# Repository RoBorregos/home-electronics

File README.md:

# home-electronics:omnibase
Electronics @HOME area, new omnibase ros2 development workspace 

For documentation check the README.md in Docs_omnibase

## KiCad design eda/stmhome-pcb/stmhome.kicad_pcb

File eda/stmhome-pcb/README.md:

# stmhome

Placa de control basada en STM32H755ZIT6, diseñada en KiCad 10.

## Contenido principal

- **STM32H755ZITx** (U1), microcontrolador principal
- **ESP32-S3-WROOM-1U** (U6), Wi-Fi / Bluetooth
- **BNO086** (U4), IMU de 9 ejes
- **TJA1051T-3** (U5), transceptor CAN
- Regulador AP7361C-33E (3.3 V), protección de polaridad con P-MOSFET y TVS en +5 V

PCB de 4 capas (100 x 85 mm): F.Cu y B.Cu para señales, In1 = GND, In2 = +3.3 V.

## Estructura

| Archivo / carpeta | Descripción |
|---|---|
| `stmhome.kicad_pro` | Proyecto de KiCad (ábrelo primero) |
| `stmhome.kicad_sch` | Hoja principal (alimentación y conectores) |
| `stm.kicad_sch` | STM32H755 |
| `esp.kicad_sch` | ESP32-S3 |
| `can.kicad_sch` | Bus CAN |
| `bno085.kicad_sch` | IMU BNO086 |
| `stmhome.kicad_pcb` | Layout de la PCB |
| `libsCH340C/` | Símbolos, footprints y modelos 3D propios |
| `scripts/` | Scripts de Python usados para acomodar componentes |

## Abrir el proyecto

1. Instala KiCad 10.
2. Abre `stmhome.kicad_pro`.
3. Si algún símbolo o footprint aparece faltante, agrega las librerías de `libsCH340C/` en
   *Preferencias > Administrar librerías de símbolos / footprints* usando la ruta
   `${KIPRJMOD}/libsCH340C/...`.

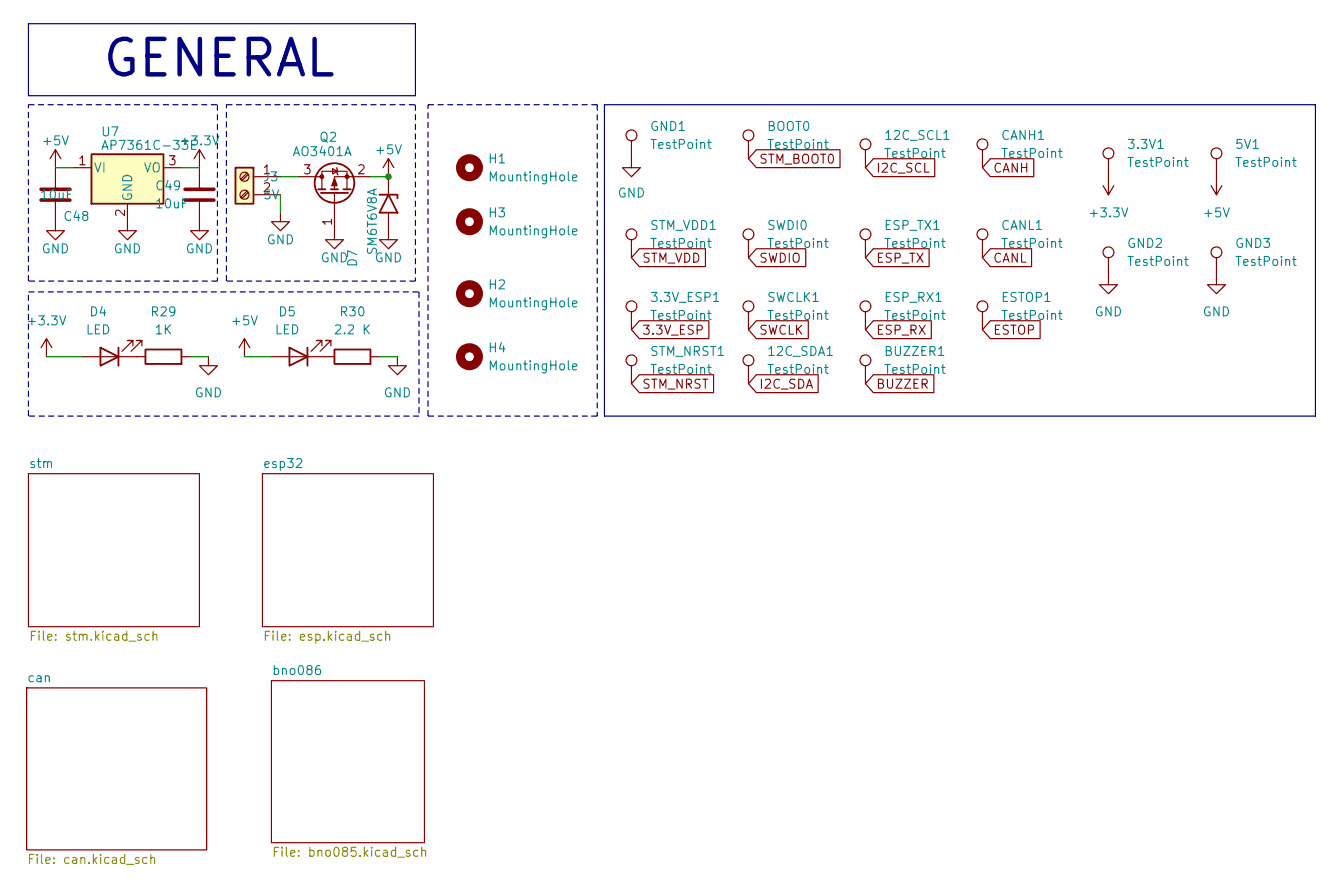
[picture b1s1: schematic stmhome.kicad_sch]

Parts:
3.3V1, 3.3V_ESP1, 5V1, 12C_SCL1, 12C_SDA1: TestPoint; TestPoint_Pad_D1.5mm
BOOT0: TestPoint; TestPoint_Pad_D1.5mm
BUZZER1: TestPoint; TestPoint_Pad_D1.5mm
C48, C49: 10uF; C_0805_2012Metric
CANH1: TestPoint; TestPoint_Pad_D1.5mm
CANL1: TestPoint; TestPoint_Pad_D1.5mm
D4, D5: LED; LED_0805_2012Metric
D7: SM6T6V8A; D_SMB
ESP_RX1: TestPoint; TestPoint_Pad_D1.5mm
ESP_TX1: TestPoint; TestPoint_Pad_D1.5mm
ESTOP1: TestPoint; TestPoint_Pad_D1.5mm
GND1, GND2, GND3: TestPoint; TestPoint_Pad_D1.5mm
H1, H2, H3, H4: MountingHole; MountingHole_3.2mm_M3
J3: 5V; TerminalBlock_Phoenix_MKDS-1,5-2-5.08_1x02_P5.08mm_Horizont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
Q2: AO3401A; SOT-23
R29: 1K; R_0805_2012Metric
R30: 2.2 K; R_0805_2012Metric
STM_NRST1: TestPoint; TestPoint_Pad_D1.5mm
STM_VDD1: TestPoint; TestPoint_Pad_D1.5mm
SWCLK1: TestPoint; TestPoint_Pad_D1.5mm
SWDI0: TestPoint; TestPoint_Pad_D1.5mm
U7: AP7361C-33E; SOT-223-3_TabPin2

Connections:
3.3V_ESP: 3.3V1.1 (1_1), 3.3V_ESP1.1 (1_1), C49.1, D4.2 (A), STM_VDD1.1 (1_1), U7.3 (VO); also elsewhere on the board
+5V: 5V1.1 (1_1), C48.1, D5.2 (A), D7.1 (A1), Q2.2 (S), U7.1 (VI); also elsewhere on the board
BUZZER: BUZZER1.1 (1_1); also elsewhere on the board
CANH: CANH1.1 (1_1); also elsewhere on the board
CANL: CANL1.1 (1_1); also elsewhere on the board
ESP_RX: ESP_RX1.1 (1_1); also elsewhere on the board
ESP_TX: ESP_TX1.1 (1_1); also elsewhere on the board
ESTOP: ESTOP1.1 (1_1); also elsewhere on the board
GND: C48.2, C49.2, D7.2 (A2), GND1.1 (1_1), GND2.1 (1_1), GND3.1 (1_1), J3.2, Q2.1 (G), R29.2, R30.2, U7.2 (GND); also elsewhere on the board
I2C_SCL: 12C_SCL1.1 (1_1); also elsewhere on the board
I2C_SDA: 12C_SDA1.1 (1_1); also elsewhere on the board
unnamed: D4.1 (K), R29.1
unnamed: D5.1 (K), R30.1
unnamed: J3.1, Q2.3 (D)
STM_BOOT0: BOOT0.1 (1_1); also elsewhere on the board
STM_NRST: STM_NRST1.1 (1_1); also elsewhere on the board
SWCLK: SWCLK1.1 (1_1); also elsewhere on the board
SWDIO: SWDI0.1 (1_1); also elsewhere on the board

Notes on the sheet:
GENERAL

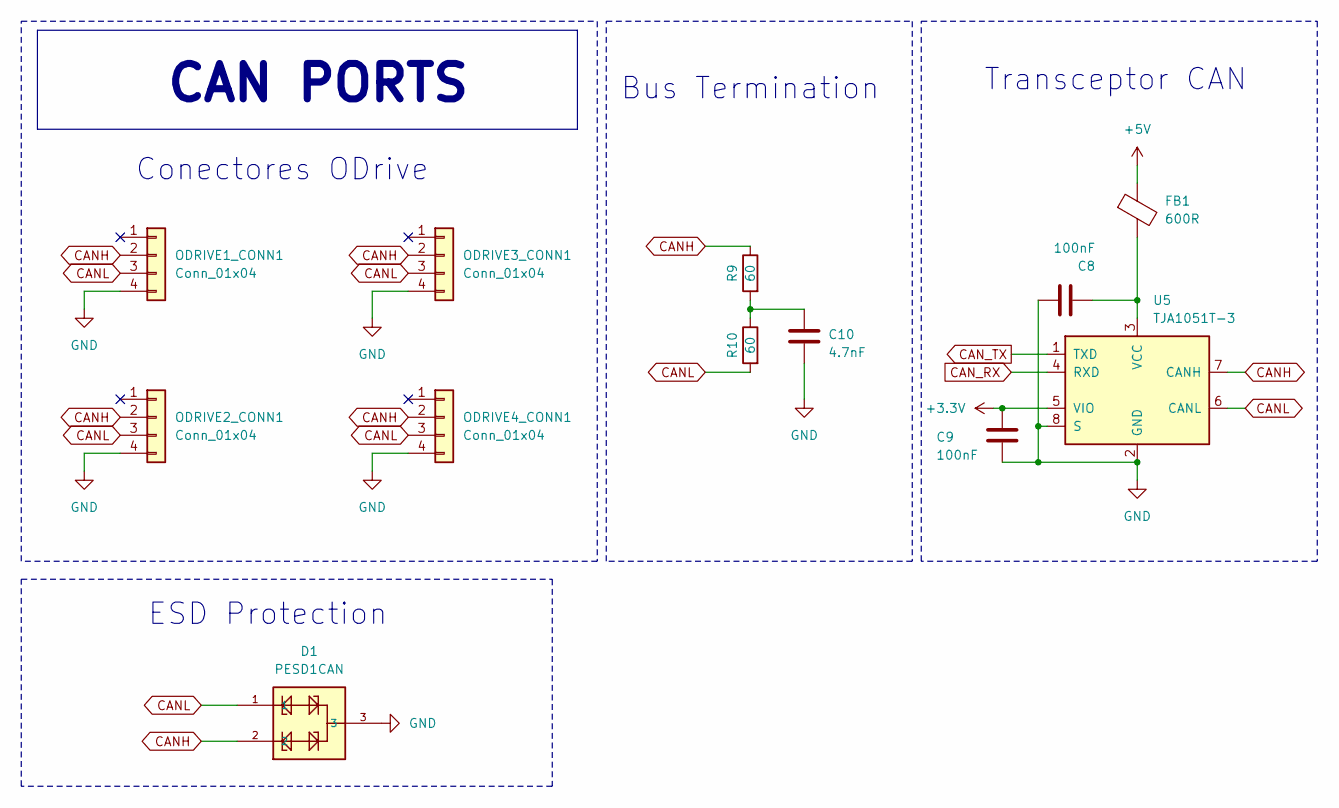
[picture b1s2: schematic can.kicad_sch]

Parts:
C8, C9: 100nF; C_0805_2012Metric
C10: 4.7nF; C_0805_2012Metric
D1: PESD1CAN; SOT23-3
FB1: 600R; L_0805_2012Metric
ODRIVE1_CONN1, ODRIVE2_CONN1, ODRIVE3_CONN1, ODRIVE4_CONN1: Conn_01x04; JST_GH_SM04B-GHS-TB_1x04-1MP_P1.25mm_Horizontal
R9, R10: 60; R_0805_2012Metric
U5: TJA1051T-3; SOIC-8_3.9x4.9mm_P1.27mm

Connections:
3.3V_ESP: C9.1, U5.5 (VIO); also elsewhere on the board
+5V: FB1.1; also elsewhere on the board
CANH: D1.2, ODRIVE1_CONN1.2, ODRIVE2_CONN1.2, ODRIVE3_CONN1.2, ODRIVE4_CONN1.2, R9.1, U5.7 (CANH); also elsewhere on the board
CANL: D1.1, ODRIVE1_CONN1.3, ODRIVE2_CONN1.3, ODRIVE3_CONN1.3, ODRIVE4_CONN1.3, R10.2, U5.6 (CANL); also elsewhere on the board
CAN_RX: U5.4 (RXD); also elsewhere on the board
CAN_TX: U5.1 (TXD); also elsewhere on the board
GND: C8.1, C9.2, C10.2, D1.3, ODRIVE1_CONN1.4, ODRIVE2_CONN1.4, ODRIVE3_CONN1.4, ODRIVE4_CONN1.4, U5.2 (GND), U5.8 (S); also elsewhere on the board
unnamed: C10.1, R9.2, R10.1
unnamed: C8.2, FB1.2, U5.3 (VCC)

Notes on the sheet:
CAN PORTS
ESD Protection
Bus Termination
Conectores ODrive
Transceptor CAN

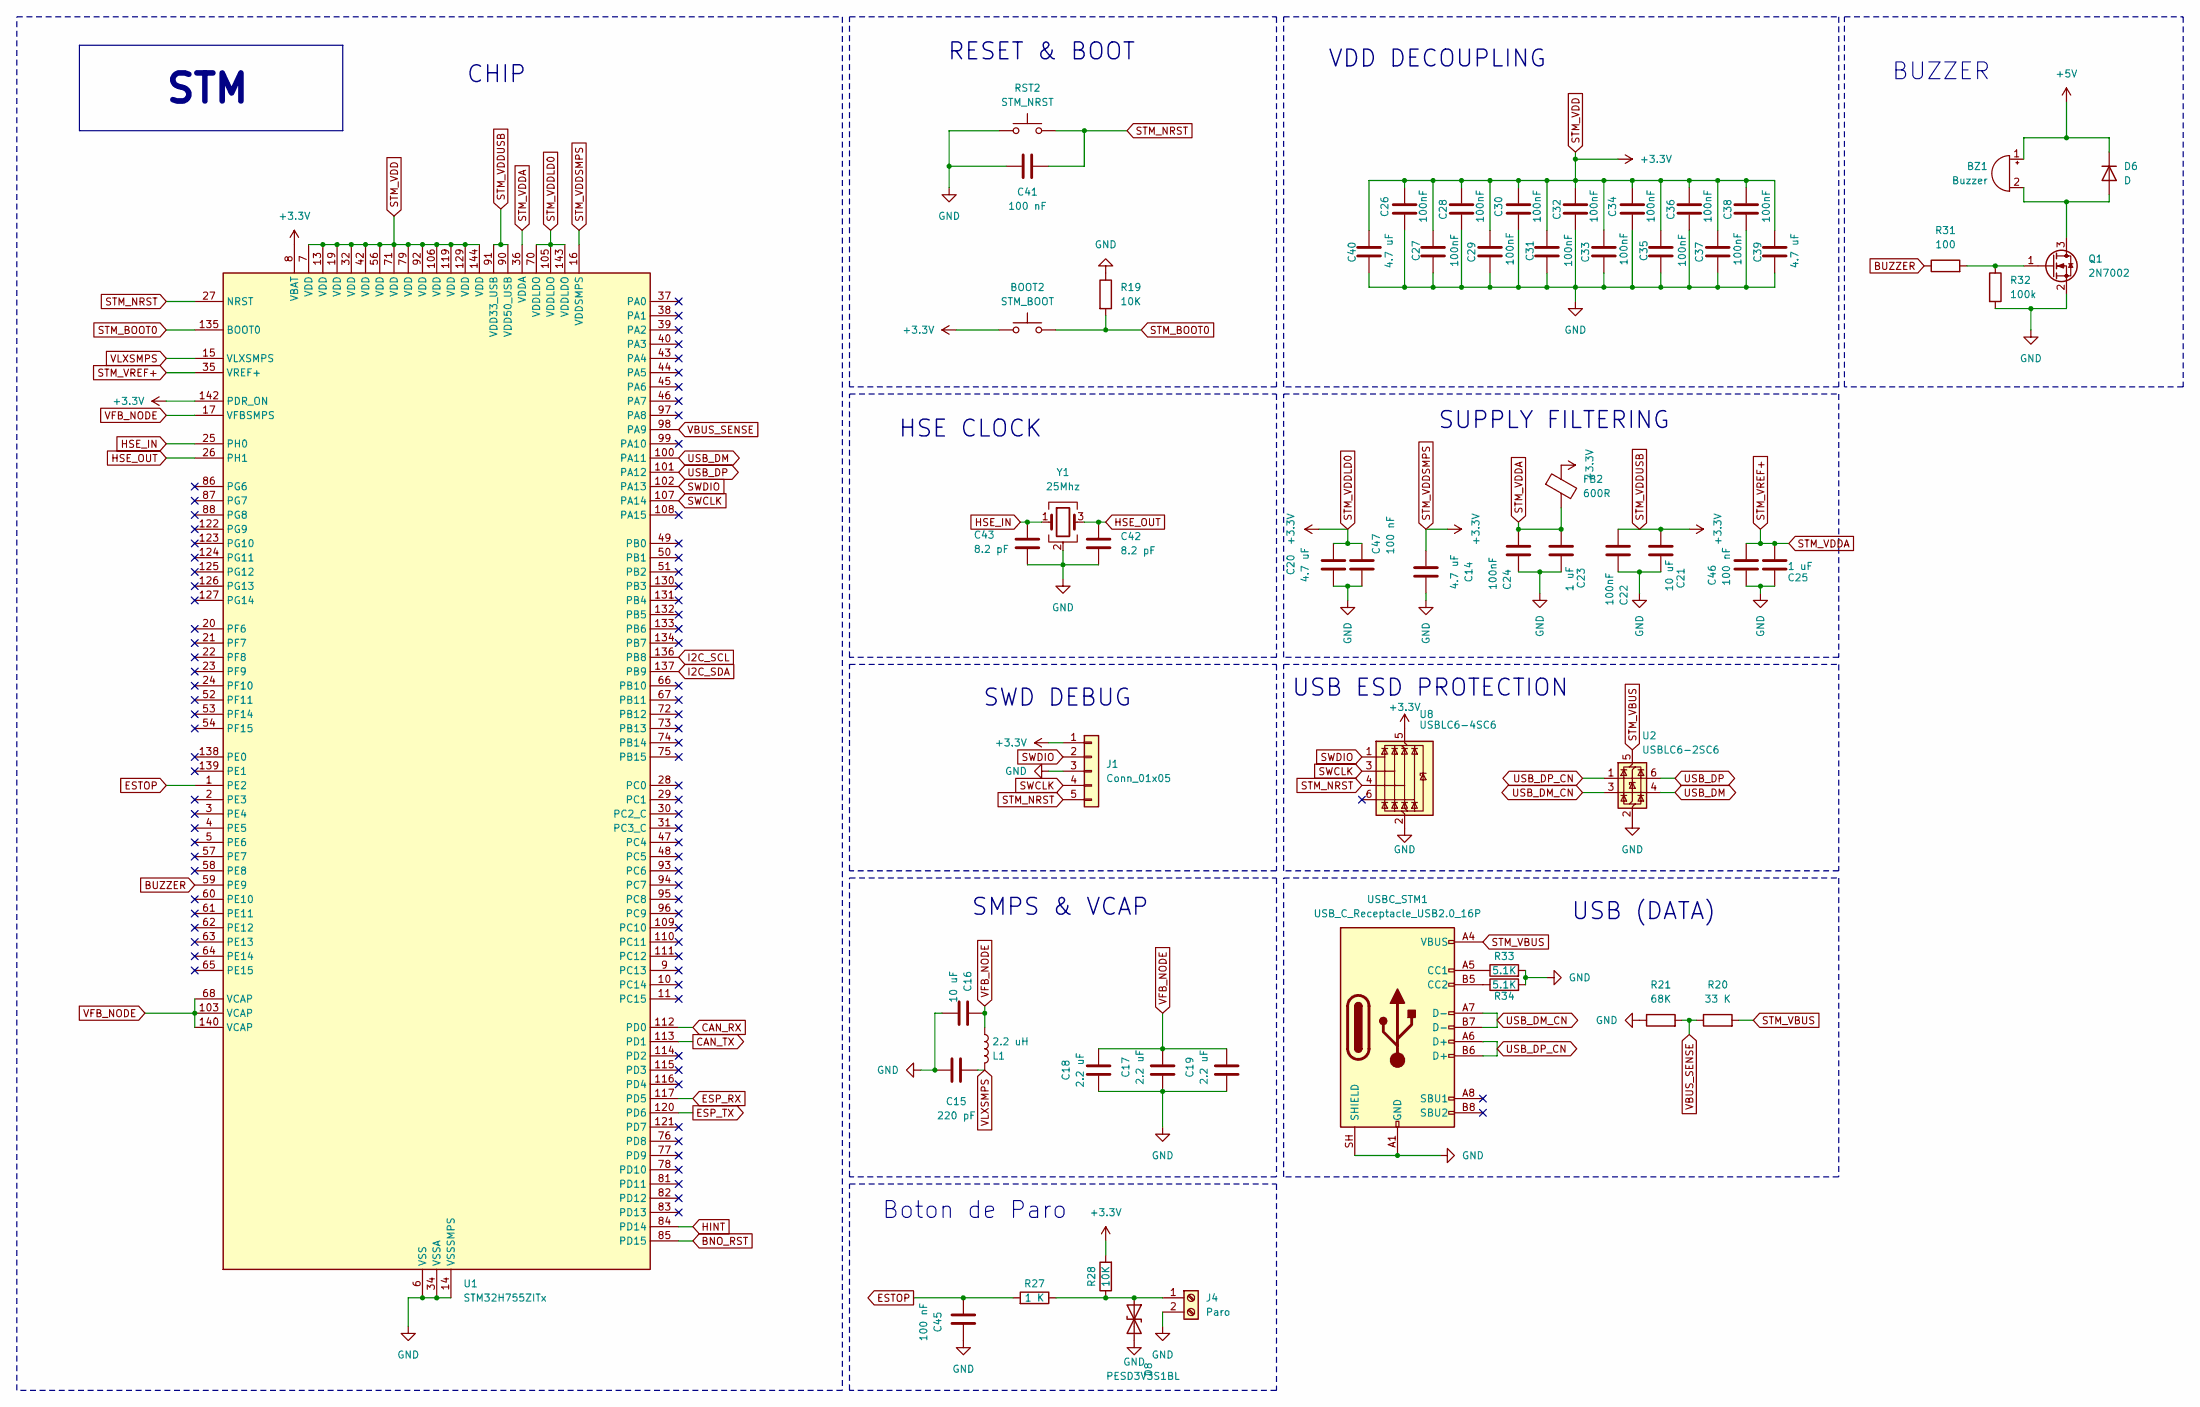
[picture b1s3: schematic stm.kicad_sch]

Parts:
BOOT2: STM_BOOT; SW_Push_1P1T_XKB_TS-1187A
BZ1: Buzzer; Buzzer_12x9.5RM7.6
C14, C20, C39, C40: 4.7 uF; C_0805_2012Metric
C15: 220 pF; C_0805_2012Metric
C16, C21: 10 uF; C_0805_2012Metric
C17, C18, C19: 2.2 uF; C_0805_2012Metric
C22, C24, C26, C27, C28, C29, C30, C31, C32, C33, C34, C35, C36, C37, C38: 100nF; C_0805_2012Metric
C23, C25: 1 uF; C_0805_2012Metric
C41, C45, C46, C47: 100 nF; C_0805_2012Metric
C42, C43: 8.2 pF; C_0805_2012Metric
D6: D; D_SOD-123
D8: PESD3V3S1BL; D_SOD-323
FB2: 600R; L_0805_2012Metric
J1: Conn_01x05; PinHeader_1x05_P2.54mm_Vertical
J4: Paro; TerminalBlock_Phoenix_MKDS-1,5-2-5.08_1x02_P5.08mm_Horizont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
L1: 2.2 uH; L_Bourns-SRN4018
Q1: 2N7002; SOT-23
R19, R28: 10K; R_0805_2012Metric
R20: 33 K; R_0805_2012Metric
R21: 68K; R_0805_2012Metric
R27: 1 K; R_0805_2012Metric
R31: 100; R_0805_2012Metric
R32: 100k; R_0805_2012Metric
R33, R34: 5.1K; R_0805_2012Metric
RST2: STM_NRST; SW_Push_1P1T_XKB_TS-1187A
U1: STM32H755ZITx; LQFP-144_20x20mm_P0.5mm
U2: USBLC6-2SC6; SOT-23-6
U8: USBLC6-4SC6; SOT-23-6
USBC_STM1: USB_C_Receptacle_USB2.0_16P; USB_C_Receptacle_GCT_USB4105-xx-A_16P_TopMnt_Horizontal
Y1: 25Mhz; Crystal_SMD_3225-4Pin_3.2x2.5mm

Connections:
3.3V_ESP: BOOT2.1, C14.1, C20.1, C21.1, C22.1, C26.1, C27.1, C28.1, C29.1, C30.1, C31.1, C32.1, C33.1, C34.1, C35.1, C36.1, C37.1, C38.1, C39.2, C40.2, C47.2, FB2.1, J1.1, R28.2, U1.7 (VDD), U1.8 (VBAT), U1.13 (VDD), U1.16 (VDDSMPS), U1.19 (VDD), U1.32 (VDD), U1.42 (VDD), U1.56 (VDD), U1.70 (VDDLDO), U1.71 (VDD), U1.79 (VDD), U1.90 (VDD50_USB), U1.91 (VDD33_USB), U1.92 (VDD), U1.105 (VDDLDO), U1.106 (VDD), U1.119 (VDD), U1.129 (VDD), U1.142 (PDR_ON), U1.143 (VDDLDO), U1.144 (VDD), U8.5 (VBUS); also elsewhere on the board
+5V: BZ1.1 (+), D6.1 (K); also elsewhere on the board
BNO_RST: U1.85 (PD15); also elsewhere on the board
BUZZER: R31.1, U1.59 (PE9); also elsewhere on the board
CAN_RX: U1.112 (PD0); also elsewhere on the board
CAN_TX: U1.113 (PD1); also elsewhere on the board
ESP_RX: U1.117 (PD5); also elsewhere on the board
ESP_TX: U1.120 (PD6); also elsewhere on the board
ESTOP: C45.1, R27.2, U1.1 (PE2); also elsewhere on the board
GND: C14.2, C15.1, C16.2, C17.1, C18.1, C19.1, C20.2, C21.2, C22.2, C23.2, C24.2, C25.1, C26.2, C27.2, C28.2, C29.2, C30.2, C31.2, C32.2, C33.2, C34.2, C35.2, C36.2, C37.2, C38.2, C39.1, C40.1, C41.2, C42.2, C43.2, C45.2, C46.1, C47.1, D8.2 (A2), J1.3, J4.2, Q1.2 (S), R19.1, R21.1, R32.2, R33.2, R34.2, RST2.1, U1.6 (VSS), U1.12 (VSS), U1.14 (VSSSMPS), U1.18 (VSS), U1.33 (VSS), U1.34 (VSSA), U1.41 (VSS), U1.55 (VSS), U1.69 (VSS), U1.80 (VSS), U1.89 (VSS), U1.104 (VSS), U1.118 (VSS), U1.128 (VSS), U1.141 (VSS), U2.2 (GND), U8.2 (GND), USBC_STM1.A1 (GND), USBC_STM1.A12 (GND), USBC_STM1.B1 (GND), USBC_STM1.B12 (GND), USBC_STM1.SH (SHIELD), Y1.2 (G), Y1.4 (G); also elsewhere on the board
HINT: U1.84 (PD14); also elsewhere on the board
HSE_IN: C43.1, U1.25 (PH0), Y1.1
HSE_OUT: C42.1, U1.26 (PH1), Y1.3
I2C_SCL: U1.136 (PB8); also elsewhere on the board
I2C_SDA: U1.137 (PB9); also elsewhere on the board
unnamed: BZ1.2 (-), D6.2 (A), Q1.3 (D)
unnamed: D8.1 (A1), J4.1, R27.1, R28.1
unnamed: Q1.1 (G), R31.2, R32.1
unnamed: R33.1, USBC_STM1.A5 (CC1)
unnamed: R34.1, USBC_STM1.B5 (CC2)
STM_BOOT0: BOOT2.2, R19.2, U1.135 (BOOT0); also elsewhere on the board
STM_NRST: C41.1, J1.5, RST2.2, U1.27 (NRST), U8.4 (I/O3); also elsewhere on the board
STM_VBUS: R20.2, U2.5 (VBUS), USBC_STM1.A4 (VBUS), USBC_STM1.A9 (VBUS), USBC_STM1.B4 (VBUS), USBC_STM1.B9 (VBUS)
STM_VDDA: C23.1, C24.1, C25.2, C46.2, FB2.2, U1.35 (VREF+), U1.36 (VDDA)
SWCLK: J1.4, U1.107 (PA14), U8.3 (I/O2); also elsewhere on the board
SWDIO: J1.2, U1.102 (PA13), U8.1 (I/O1); also elsewhere on the board
USB_DM: U1.100 (PA11), U2.4 (I/O2)
USB_DM_CN: U2.3 (I/O2), USBC_STM1.A7 (D-), USBC_STM1.B7 (D-)
USB_DP: U1.101 (PA12), U2.6 (I/O1)
USB_DP_CN: U2.1 (I/O1), USBC_STM1.A6 (D+), USBC_STM1.B6 (D+)
VBUS_SENSE: R20.1, R21.2, U1.98 (PA9)
VFB_NODE: C16.1, C17.2, C18.2, C19.2, L1.2, U1.17 (VFBSMPS), U1.68 (VCAP), U1.103 (VCAP), U1.140 (VCAP)
VLXSMPS: C15.2, L1.1, U1.15 (VLXSMPS)

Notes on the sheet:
USB ESD PROTECTION
HSE CLOCK
SUPPLY FILTERING
VDD DECOUPLING
RESET & BOOT
STM
USB (DATA)
SWD DEBUG
CHIP
Boton de Paro
BUZZER
SMPS & VCAP

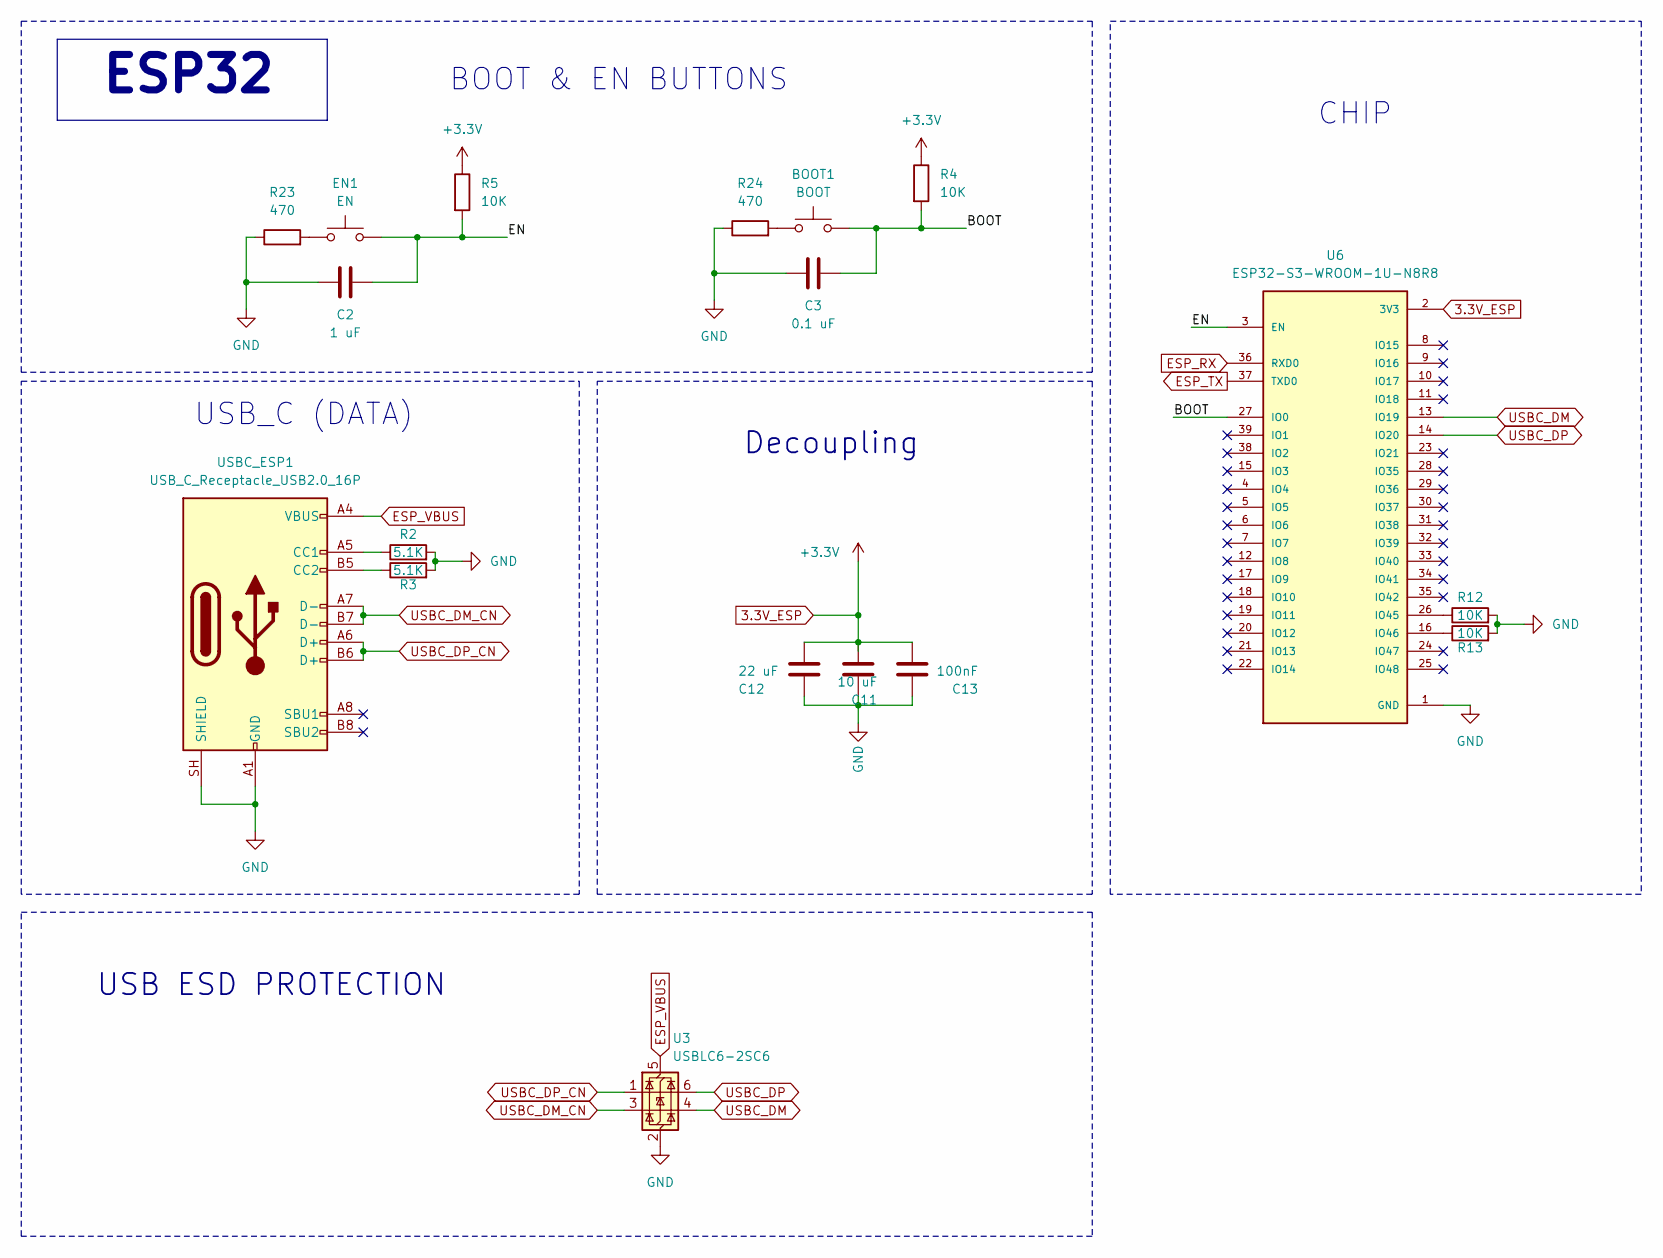
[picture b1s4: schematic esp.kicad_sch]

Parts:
BOOT1: BOOT; SW_Push_1P1T_XKB_TS-1187A
C2: 1 uF; C_0805_2012Metric
C3: 0.1 uF; C_0805_2012Metric
C11: 10 uF; C_0805_2012Metric
C12: 22 uF; C_0805_2012Metric
C13: 100nF; C_0805_2012Metric
EN1: EN; SW_Push_1P1T_XKB_TS-1187A
R2, R3: 5.1K; R_0805_2012Metric
R4, R5, R12, R13: 10K; R_0805_2012Metric
R23, R24: 470; R_0805_2012Metric
U3: USBLC6-2SC6; SOT-23-6
U6: ESP32-S3-WROOM-1U-N8R8; XCVR_ESP32-S3-WROOM-1U-N8R8; PARTREV v1.1
USBC_ESP1: USB_C_Receptacle_USB2.0_16P; USB_C_Receptacle_GCT_USB4105-xx-A_16P_TopMnt_Horizontal

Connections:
3.3V_ESP: C11.1, C12.1, C13.1, R4.1, R5.1, U6.2 (3V3); also elsewhere on the board
/esp32/BOOT: BOOT1.2, C3.1, R4.2, U6.27 (IO0)
/esp32/EN: C2.1, EN1.2, R5.2, U6.3 (EN)
ESP_RX: U6.36 (RXD0); also elsewhere on the board
ESP_TX: U6.37 (TXD0); also elsewhere on the board
ESP_VBUS: U3.5 (VBUS), USBC_ESP1.A4 (VBUS), USBC_ESP1.A9 (VBUS), USBC_ESP1.B4 (VBUS), USBC_ESP1.B9 (VBUS)
GND: C2.2, C3.2, C11.2, C12.2, C13.2, R2.2, R3.2, R12.2, R13.2, R23.1, R24.1, U3.2 (GND), U6.1 (GND), U6.40 (GND), U6.41_1 (GND), U6.41_2 (GND), U6.41_3 (GND), U6.41_4 (GND), U6.41_5 (GND), U6.41_6 (GND), U6.41_7 (GND), U6.41_8 (GND), U6.41_9 (GND), USBC_ESP1.A1 (GND), USBC_ESP1.A12 (GND), USBC_ESP1.B1 (GND), USBC_ESP1.B12 (GND), USBC_ESP1.SH (SHIELD); also elsewhere on the board
unnamed: BOOT1.1, R24.2
unnamed: EN1.1, R23.2
unnamed: R12.1, U6.26 (IO45)
unnamed: R13.1, U6.16 (IO46)
unnamed: R2.1, USBC_ESP1.A5 (CC1)
unnamed: R3.1, USBC_ESP1.B5 (CC2)
USBC_DM: U3.4 (I/O2), U6.13 (IO19)
USBC_DM_CN: U3.3 (I/O2), USBC_ESP1.A7 (D-), USBC_ESP1.B7 (D-)
USBC_DP: U3.6 (I/O1), U6.14 (IO20)
USBC_DP_CN: U3.1 (I/O1), USBC_ESP1.A6 (D+), USBC_ESP1.B6 (D+)

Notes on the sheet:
ESP32
CHIP
Decoupling
USB_C (DATA)
USB ESD PROTECTION
BOOT & EN BUTTONS

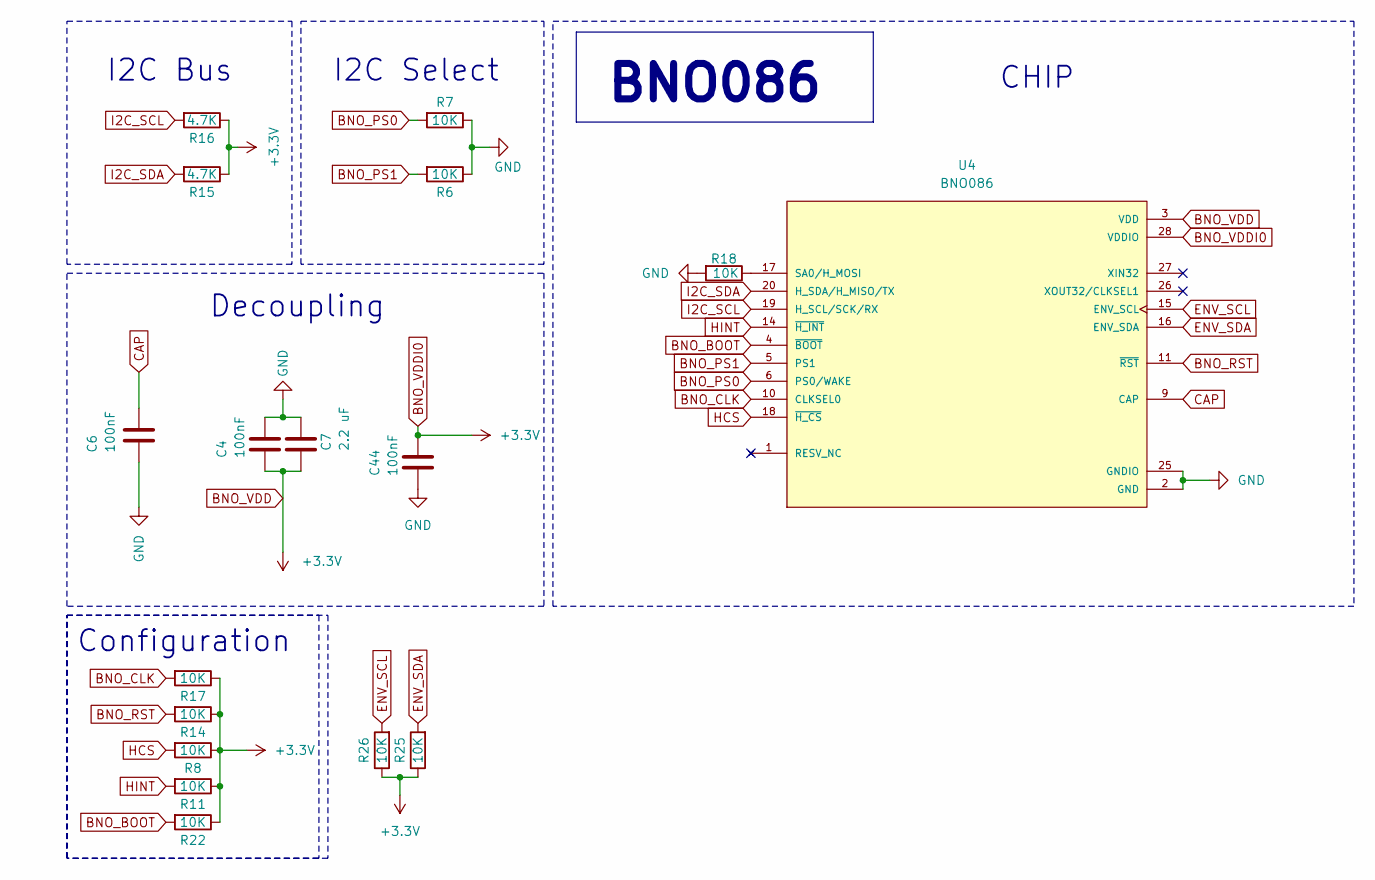
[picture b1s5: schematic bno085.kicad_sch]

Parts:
C4, C6, C44: 100nF; C_0805_2012Metric
C7: 2.2 uF; C_0805_2012Metric
R6, R7, R8, R11, R14, R17, R18, R22, R25, R26: 10K; R_0805_2012Metric
R15, R16: 4.7K; R_0805_2012Metric
U4: BNO086; IC_BNO085; PARTREV v1.17

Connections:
3.3V_ESP: C4.1, C7.1, C44.2, R8.1, R11.1, R14.1, R15.1, R16.1, R17.1, R22.1, R25.1, R26.1, U4.3 (VDD), U4.28 (VDDIO); also elsewhere on the board
BNO_BOOT: R22.2, U4.4 (~BOOT)
BNO_CLK: R17.2, U4.10 (CLKSEL0)
BNO_PS0: R7.2, U4.6 (PS0/WAKE)
BNO_PS1: R6.2, U4.5 (PS1)
BNO_RST: R14.2, U4.11 (~RST); also elsewhere on the board
CAP: C6.1, U4.9 (CAP)
ENV_SCL: R26.2, U4.15 (ENV_SCL)
ENV_SDA: R25.2, U4.16 (ENV_SDA)
GND: C4.2, C6.2, C7.2, C44.1, R6.1, R7.1, R18.2, U4.2 (GND), U4.25 (GNDIO); also elsewhere on the board
HCS: R8.2, U4.18 (~H_CS)
HINT: R11.2, U4.14 (~H_INT); also elsewhere on the board
I2C_SCL: R16.2, U4.19 (H_SCL/SCK/RX); also elsewhere on the board
I2C_SDA: R15.2, U4.20 (H_SDA/H_MISO/TX); also elsewhere on the board
unnamed: R18.1, U4.17 (SA0/H_MOSI)

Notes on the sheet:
I2C Select
Decoupling
CHIP
BNO086
I2C Bus
Configuration

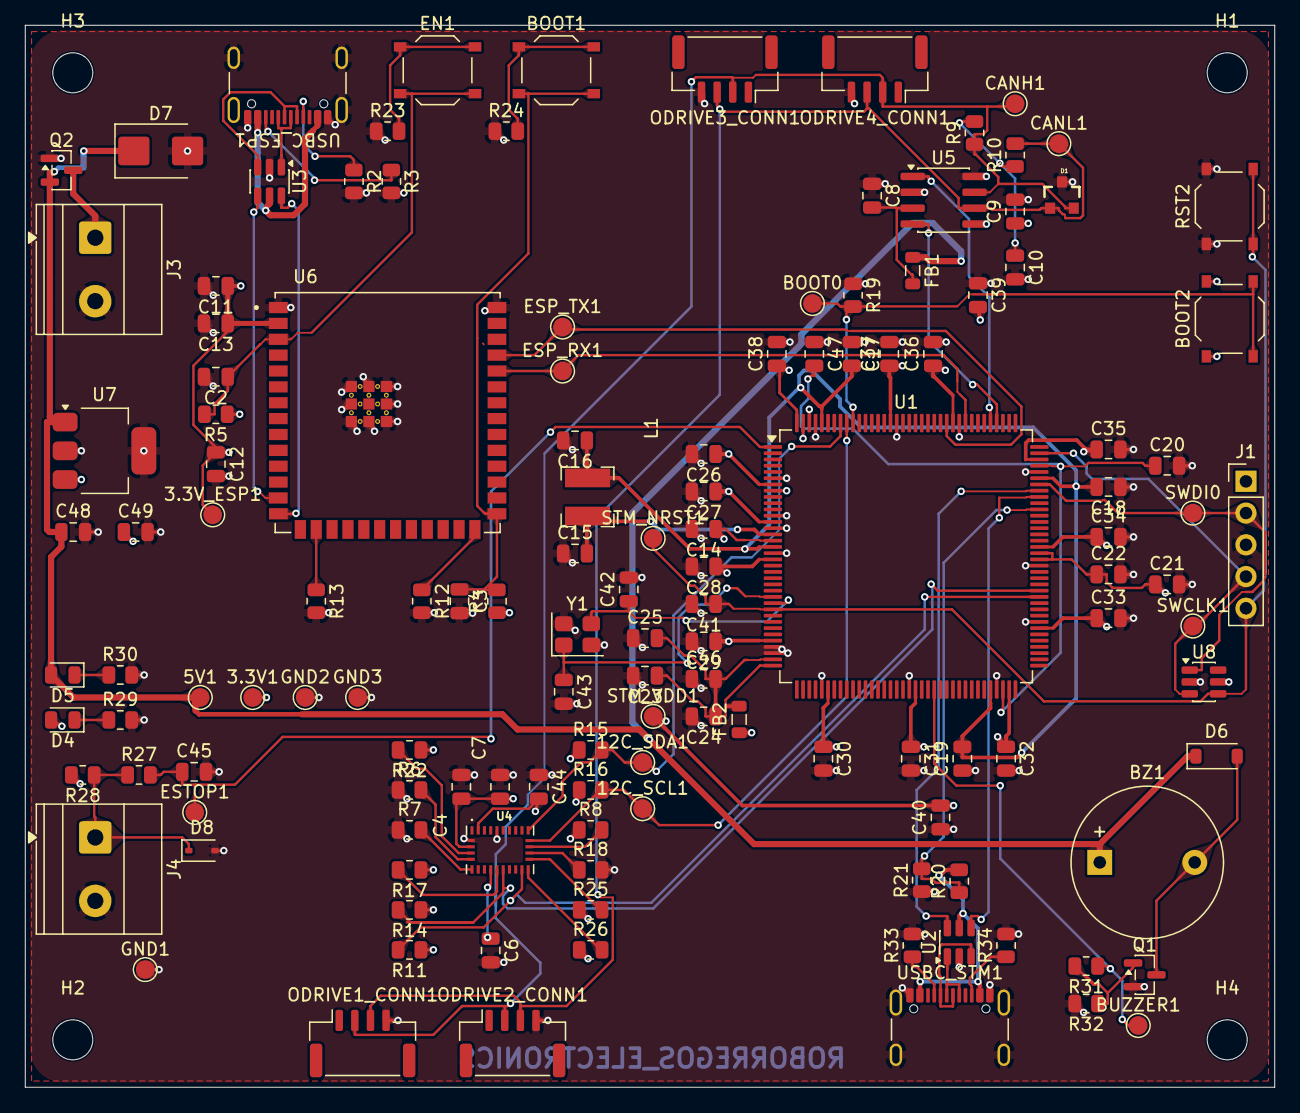
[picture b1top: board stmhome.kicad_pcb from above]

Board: 4 copper layers, 100.0 x 85.0 mm, 137 parts (0 on the bottom side), 62 nets.

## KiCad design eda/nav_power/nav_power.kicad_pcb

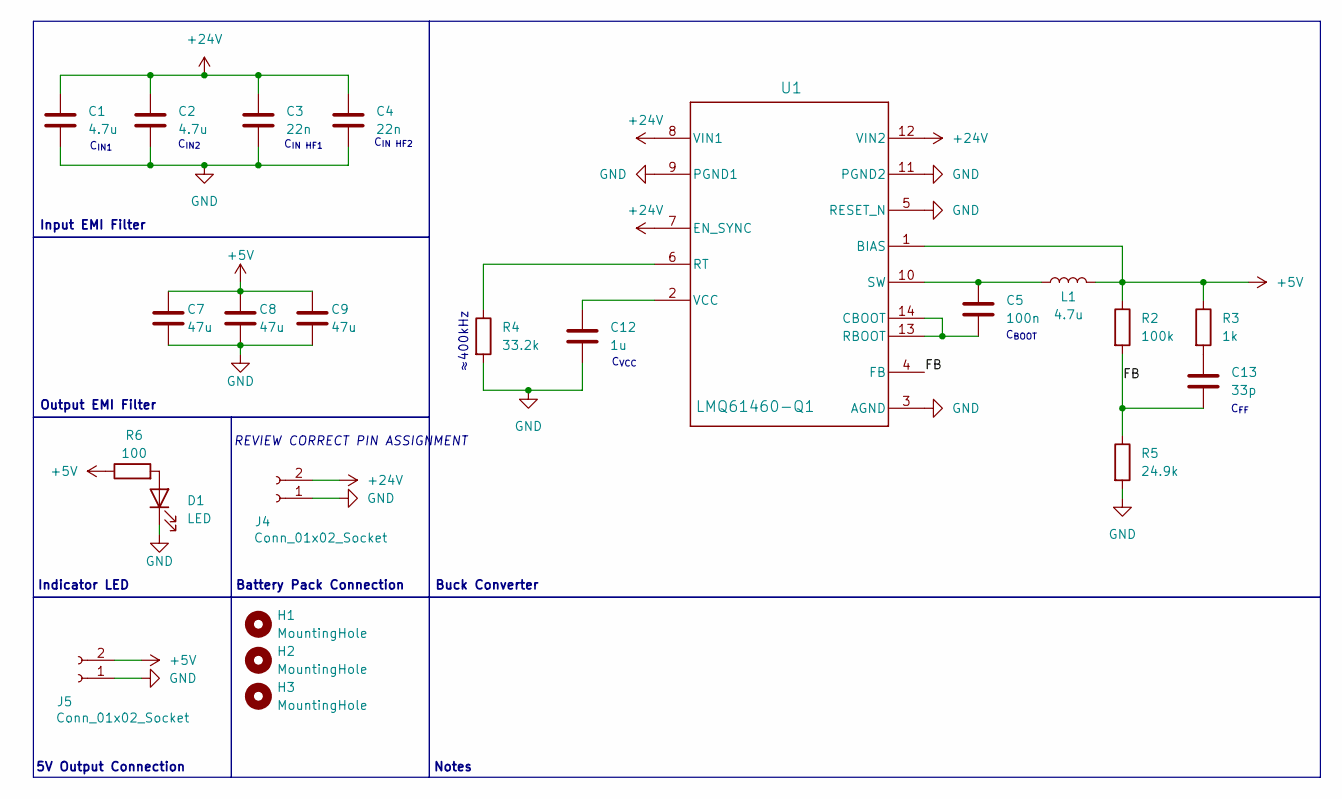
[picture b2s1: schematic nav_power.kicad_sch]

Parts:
C1, C2: 4.7u; C_1210_3225Metric_Pad1.33x2.70mm_HandSolder
C3, C4: 22n; C_0402_1005Metric_Pad0.74x0.62mm_HandSolder
C5: 100n; C_0603_1608Metric_Pad1.08x0.95mm_HandSolder
C7, C8, C9: 47u; C_1210_3225Metric_Pad1.33x2.70mm_HandSolder
C12: 1u; C_0805_2012Metric_Pad1.18x1.45mm_HandSolder
C13: 33p; C_0805_2012Metric_Pad1.18x1.45mm_HandSolder
D1: LED; LED_1206_3216Metric_Pad1.42x1.75mm_HandSolder
H1, H2, H3: MountingHole; MountingHole_2.2mm_M2_Pad_TopBottom
J4, J5: Conn_01x02_Socket; JST_VH_B2P-VH_1x02_P3.96mm_Vertical
L1: 4.7u; L_Wuerth_XHMI-6060
R2: 100k; R_0603_1608Metric_Pad0.98x0.95mm_HandSolder
R3: 1k; R_1206_3216Metric_Pad1.30x1.75mm_HandSolder
R4: 33.2k; R_0603_1608Metric_Pad0.98x0.95mm_HandSolder
R5: 24.9k; R_0603_1608Metric_Pad0.98x0.95mm_HandSolder
R6: 100; R_0603_1608Metric_Pad0.98x0.95mm_HandSolder
U1: LMQ61460-Q1; RJR0014A-MFG

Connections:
+5V: C7.1, C8.1, C9.1, J5.2, L1.2, R2.1, R3.1, R6.1, U1.1 (BIAS)
+24V: C1.1, C2.1, C3.1, C4.1, J4.2, U1.7 (EN_SYNC), U1.8 (VIN1), U1.12 (VIN2)
/FB: C13.2, R2.2, R5.1, U1.4 (FB)
GND: C1.2, C2.2, C3.2, C4.2, C7.2, C8.2, C9.2, C12.2, D1.1 (K), J4.1, J5.1, R4.2, R5.2, U1.3 (AGND), U1.5 (RESET_N), U1.9 (PGND1), U1.11 (PGND2)
unnamed: C13.1, R3.2
unnamed: D1.2 (A), R6.2
unnamed: C5.2, U1.13 (RBOOT), U1.14 (CBOOT)
unnamed: R4.1, U1.6 (RT)
unnamed: C5.1, L1.1, U1.10 (SW)
unnamed: C12.1, U1.2 (VCC)

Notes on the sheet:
C_{FF}
C_{BOOT}
Indicator LED
C_{IN HF2}
Notes
≈400kHz
Output EMI Filter
5V Output Connection
REVIEW CORRECT PIN ASSIGNMENT
Buck Converter
C_{VCC}
C_{IN2}
Input EMI Filter
C_{IN HF1}
Battery Pack Connection
C_{IN1}

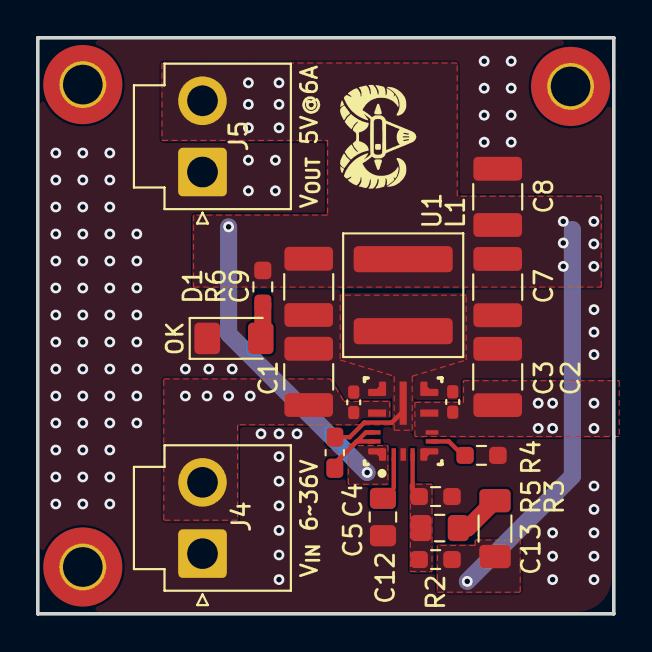
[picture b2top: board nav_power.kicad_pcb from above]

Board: 4 copper layers, 32.0 x 32.0 mm, 23 parts (0 on the bottom side), 10 nets.

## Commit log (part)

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2025-01-23 Schema update
2025-01-23 Added real test project
2025-01-23 Update changes
2025-01-25 docs
2025-01-25 docs: pcb blocks & desc.
2025-01-30 added frida docs
2025-02-06 Added Power Info
2025-03-24 Create Arduino
2025-03-24 Create Python
2025-03-24 Update Arduino
2025-03-24 Update Python
2025-04-27 Create Python2
2025-04-27 Create Arduino2
2025-04-28 GripperAltaBajaI
2025-04-29 Codigo del Gripper pero con conexion Bluetooth
2025-04-29 Rename Arduino to Arduino.ino
2025-04-29 Rename Arduino2 to Arduino2.ino
2025-04-29 Rename Python to Python.py
2025-04-29 Rename Python2 to Python2.py
2025-05-24 initial commit added serial_comm_node
2025-05-24 initial omnibase docs
2025-05-26 added some RX topics, readme update
2025-05-26 changed stm32 project repo link
2025-05-28 gain changes, succ motor vel control test
